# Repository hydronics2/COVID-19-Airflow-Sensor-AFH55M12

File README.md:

# Airflow Sensor - Automotive Sensor AFH55M12

## Project Description ([from Helpful Engineering](https://www.helpfulengineering.org/))
The intent here is to create a monitoring device, based on a mass airflow meter, that can be used when splitting a ventilator into two or more patients. This will allow staff to monitor individual patients while being controlled by one device in extreme situations where the number of ventilators are not enough to handle the number of patients. The readout should be visible locally on the device and there may need to be parameters input by staff to create a safe operating range and to possibly create alarms when the system is measuring an out of range parameter.

### [Project Requirements](https://docs.google.com/document/d/17Ps910A2vRwnM4EM6F-71GNG1XNa0PaeImd53F7428c/edit?usp=sharing)

This is a quick study of using an inexpensive off-the-shelf automotive airflow type sensor.

Reading from an automotive mass airflow sensor using a microController 12bit ADC, 20ms interval

### --- Updates April 8th -- Assembled PCB, airflow sensor, on 3d print

The model by @john Grano is [here](https://github.com/hydronics2/COVID-19-Airflow-Sensor-AFH55M12/blob/master/3d-prints/MAF_Chamber_Body_V3.stl). Although this appears to prove the technology is working, we're currently pivoting to a manifold type layout...
- to centralize all user interface displays next to the mechanical ventilator
- simplifies to one PCB
- one power supply
- serves multiple flow sensors

### --- Updates April 6th -- 3D print by @john Grano on Slack

###  --- Updates April 4th -- Arduino Sketch show airflow
The arduino sketch shows estimated ariflow volume in mL.

###  --- Updates Wednesday March 28th -- Airflow testing

Installed sensor in a 1" tube. Only showing inhales
- used previous estimates for a medium inhale breath as ~1150mL to calibrate sensor

### Sensor Availability
The sensor shows up as multiple part values. It fits a 1998 Nissan/Datsun Truck Frontier 2WD 2.4L FI 4cyl among other years and other vehicles.
- [China](https://www.aliexpress.com/item/32989444018.html?spm=a2g0o.cart.0.0.74dd3c00g1XL5u&mp=1)
- [US Supplier](https://www.amazon.com/gp/product/B074FZMGWG/ref=ppx_yo_dt_b_asin_title_o00_s00?ie=UTF8&psc=1)
- [local supplier oreilly](https://www.oreillyauto.com/search/1998/nissan/frontier?q=MF21219)
- [local supplier auto-zone](https://www.autozone.com/engine-management/mass-air-flow-sensor/duralast-new-mass-air-flow-sensor-dl-3025/337334_0_4995?&searchText=DL3025)

#### Pinout
- Pin A - Empty
- Pin B - 7-12V DC, 90-115mA
- Pin C - Ground
- Pin D Signal

#### Parts List
- oled display is a generic [0.96" 128X64 I2C OLED](https://www.ebay.com/sch/i.html?_from=R40&_trksid=m570.l1313&_nkw=0.96%22+128X64+I2C+OLED&_sacat=0)
- BME280 pressure sensor [828-1063-1-ND](https://www.digikey.com/product-detail/en/bosch-sensortec/BME280/828-1063-1-ND/6136314)

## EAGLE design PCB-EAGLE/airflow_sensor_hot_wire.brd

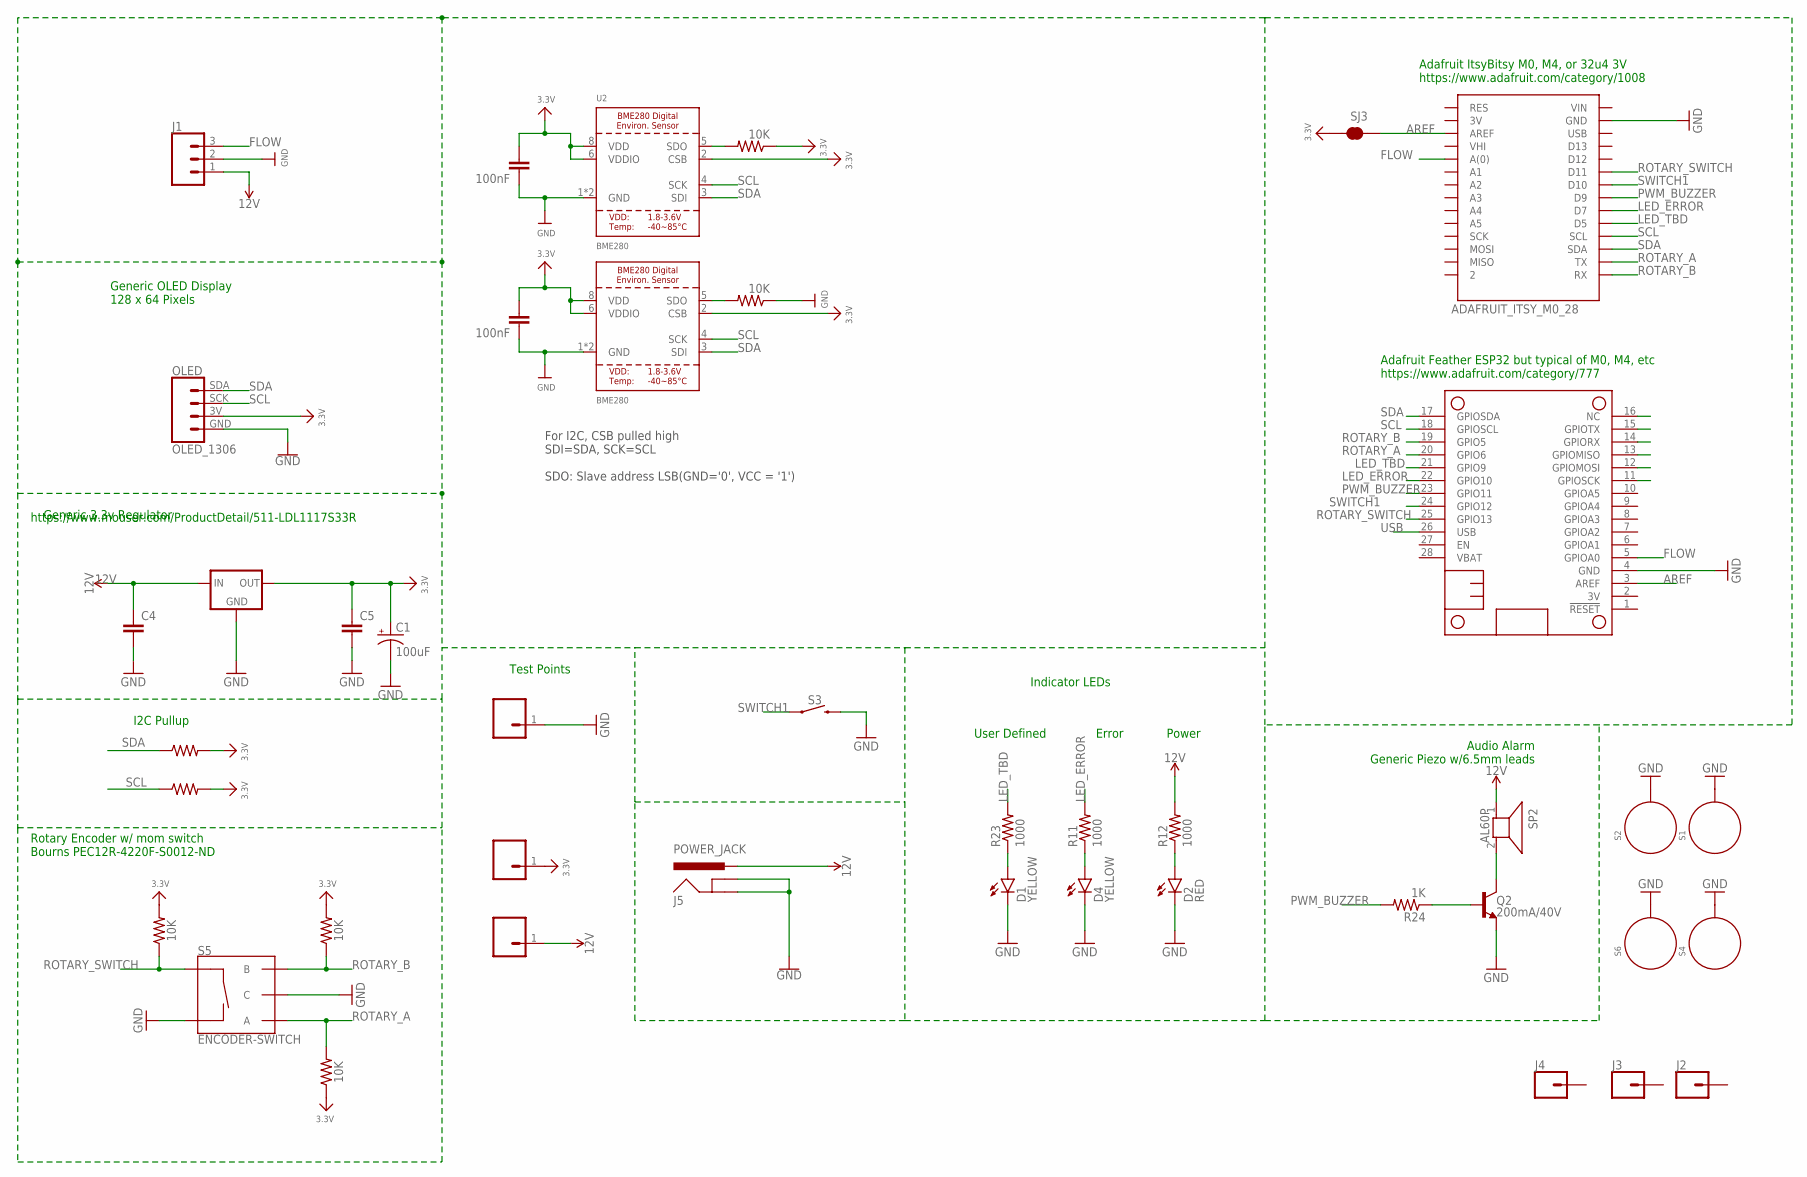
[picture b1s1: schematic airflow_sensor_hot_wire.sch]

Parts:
3V_REGULATOR: LDL1117_5V_REG; SOT223
C1: 100uF; CPOL-RADIAL-2.5MM-6.5MM
C4, C5: CAP-0805; 0805
C10, C12: 100nF; 0805
D1, D4: YELLOW; LED-1206
D2: RED; LED-1206
J1: CONN_03-SCREW-5MM; SCREWTERMINAL-5MM-3
J2, J3, J4: CONN_01; 1X01
J5: POWER_JACK; POWER_JACK_PTH
MS2: FEATHERWING_NODIM; FEATHERWING_DIM
Q2: 200mA/40V; TO-92
R1, R2, R26, R27, R28: 10K; 0805
R11, R12, R23: 1000; 0805
R21, R22: 0.3; 0805
R24: 1K; 0805
S1, S2, S4, S6: STANDOFF_ELECTRICAL5-32; STANDOFF_ELECTRICAL_5_32
S3: MOMENTARY-SWITCH-SPST-PTH-6.0MM-KIT; TACTILE_SWITCH_PTH_6.0MM_KIT
S5: ENCODER-SWITCH; ROTARY_ENC_PLAIN
SJ3: PWR-LED; PAD-JUMPER-2-NC_BY_TRACE_NO_SILK
SP2: AL60P
U2, U4: BME280
U$1: OLED_1306
U$20, U$31, U$40: CONN_0138MILL; 1X01-40MILL
U$45: ADAFRUIT_ITSY_M0_28; ADAFRUIT_ITS_MO_28

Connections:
3.3V: 3V_REGULATOR.2 (OUT), 3V_REGULATOR.4 (OUT), C1.1 (+), C5.1, C10.1, C12.1, R2.1, R21.2, R22.2, R26.2, R27.1, R28.2, SJ3.2, U2.2 (CSB), U2.6 (VDDIO), U2.8 (VDD), U4.2 (CSB), U4.6 (VDDIO), U4.8 (VDD), U$1.3V (VCC), U$20.1
12V: 3V_REGULATOR.3 (IN), C4.1, J1.1, J5.PWR, R12.2, SP2.1, U$40.1
AREF: MS2.3 (AREF), SJ3.1, U$45.AREF
FLOW: J1.3, MS2.5 (GPIOA0), U$45.A0 (A(0))
GND: 3V_REGULATOR.1 (GND), C1.2 (-), C4.2, C5.2, C10.2, C12.2, D1.C, D2.C, D4.C, J1.2, J5.GND, J5.GNDBREAK, MS2.4 (GND), Q2.1 (E), R1.1, S1.P1, S2.P1, S3.3 (2), S4.P1, S5.C, S5.SW-, S6.P1, U2.1 (GND), U2.7 (GND), U4.1 (GND), U4.7 (GND), U$1.GND, U$31.1, U$45.GND
LED_ERROR: MS2.22 (GPIO10), R11.2, U$45.D7
LED_TBD: MS2.21 (GPIO9), R23.2, U$45.D5
unnamed: D2.A, R12.1
unnamed: D1.A, R23.1
unnamed: R1.2, U4.5 (SDO)
unnamed: R2.2, U2.5 (SDO)
unnamed: Q2.3 (C), SP2.2
unnamed: Q2.2 (B), R24.1
unnamed: D4.A, R11.1
PWM_BUZZER: MS2.23 (GPIO11), R24.2, U$45.D9
ROTARY_A: MS2.20 (GPIO6), R27.2, S5.A, U$45.TX
ROTARY_B: MS2.19 (GPIO5), R26.1, S5.B, U$45.RX
ROTARY_SWITCH: MS2.25 (GPIO13), R28.1, S5.SW+, U$45.D11
SCL: MS2.18 (GPIOSCL), R22.1, U2.4 (SCK), U4.4 (SCK), U$1.SCK, U$45.SCL
SDA: MS2.17 (GPIOSDA), R21.1, U2.3 (SDI), U4.3 (SDI), U$1.SDA, U$45.SDA
SWITCH1: MS2.24 (GPIO12), S3.1, U$45.D10
USB: MS2.26 (USB)

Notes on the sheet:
I2C Pullup
Generic OLED Display 128 x 64 Pixels
Adafruit ItsyBitsy M0, M4, or 32u4 3V https://www.adafruit.com/category/1008
Adafruit Feather ESP32 but typical of M0, M4, etc https://www.adafruit.com/category/777
Test Points
Indicator LEDs
Power
Error
User Defined
Audio Alarm Generic Piezo w/6.5mm leads
Rotary Encoder w/ mom switch Bourns PEC12R-4220F-S0012-ND
Generic 3.3v Regulator
https://www.mouser.com/ProductDetail/511-LDL1117S33R
For I2C, CSB pulled high SDI=SDA, SCK=SCL SDO: Slave address LSB(GND='0', VCC = '1')

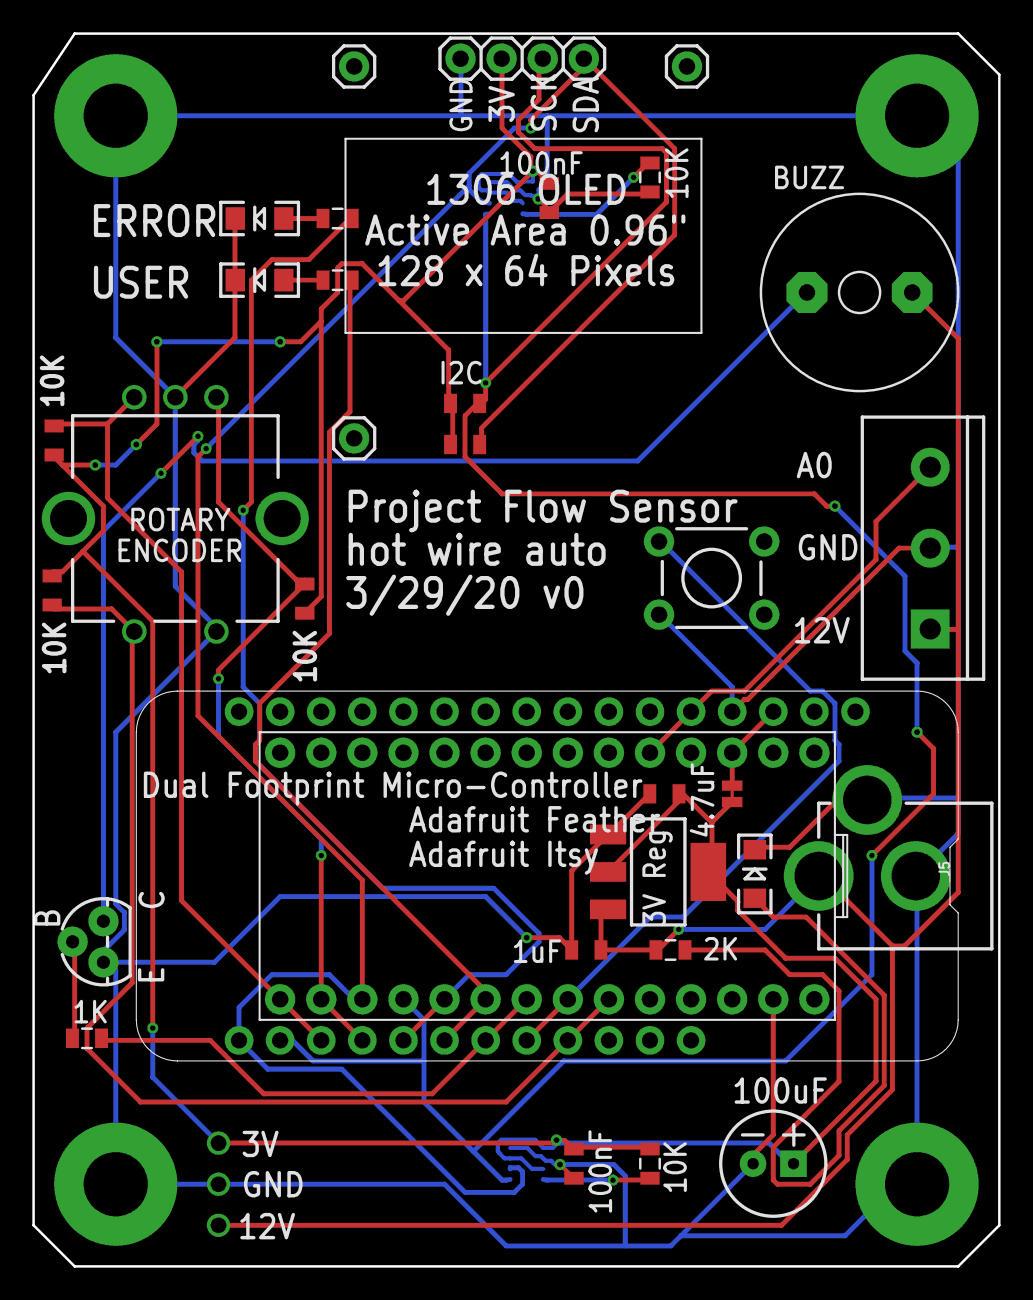
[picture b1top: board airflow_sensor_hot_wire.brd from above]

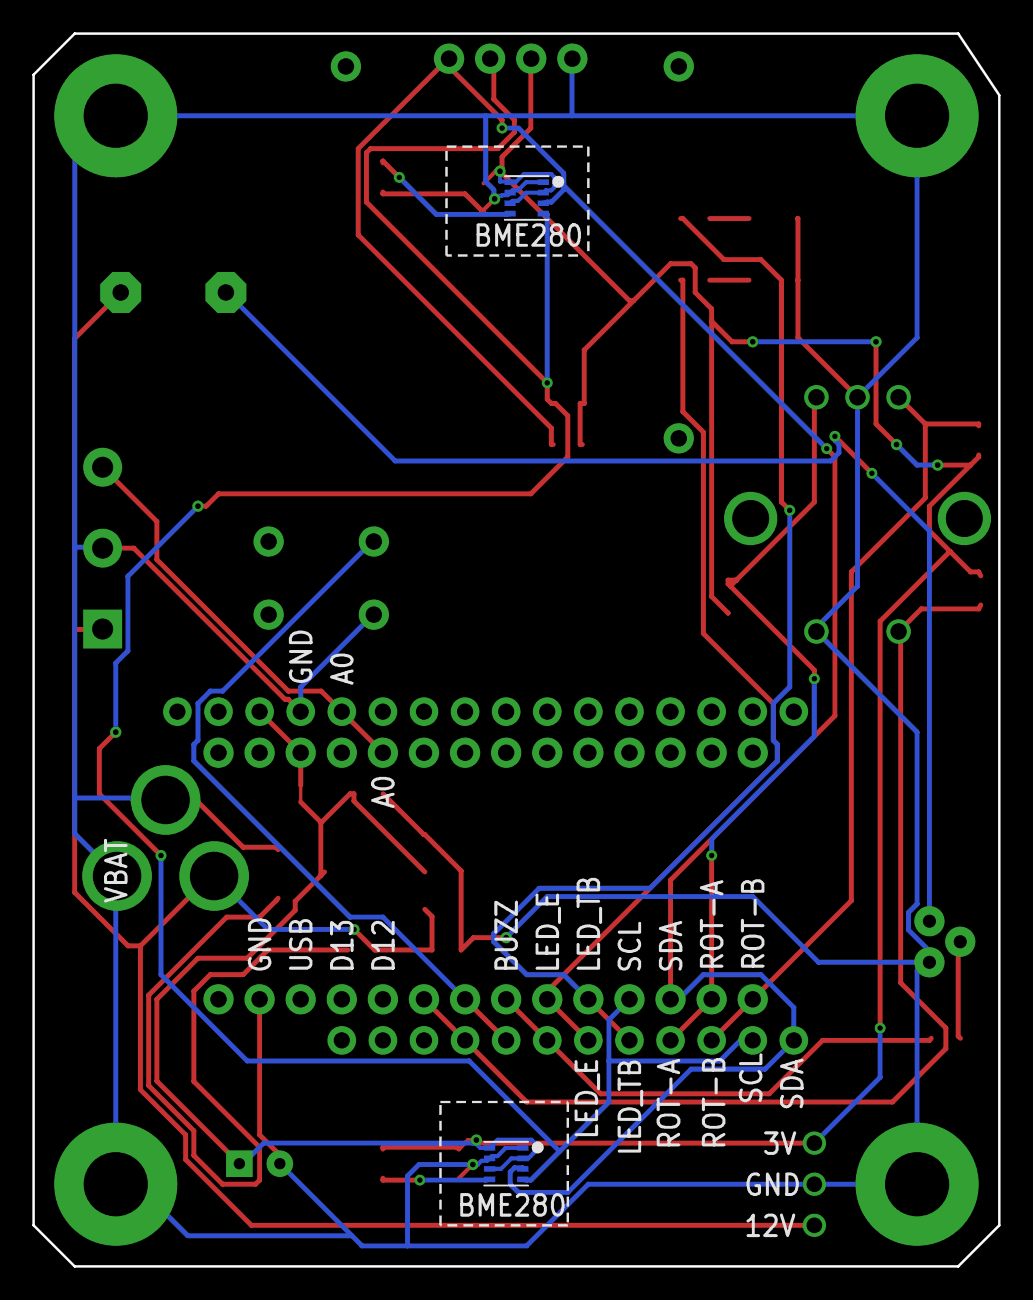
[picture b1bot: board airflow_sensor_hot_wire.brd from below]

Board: 2 copper layers, 59.7 x 76.2 mm, 42 parts (2 on the bottom side), 21 nets.

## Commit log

2020-03-29 3/28/20 data
2020-03-30 added images
2020-03-30 add eagle files
2020-03-30 schematic update
2020-03-30 add pic
2020-04-05 added arduino sketch and video
2020-04-05 updated sketch
2020-04-06 added pic of model
2020-04-06 added stl
2020-04-09 added 3d print file
2020-04-09 updates names
2020-04-22 updated with SLM conversion
2020-04-22 updated with curve fit calibration equation for SLM
2020-04-22 updated with Patrick's curve fit equation
2020-04-22 added one ms to the volume calculation

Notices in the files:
parts and their libraries:
SparkFun-Capacitors: Licensing: Creative Commons ShareAlike 4.0 International - https://creativecommons.org/licenses/by-sa/4.0
microbuilder: This work is placed in the public domain, and may be freely used for commercial and non-commercial work with the following conditions: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
